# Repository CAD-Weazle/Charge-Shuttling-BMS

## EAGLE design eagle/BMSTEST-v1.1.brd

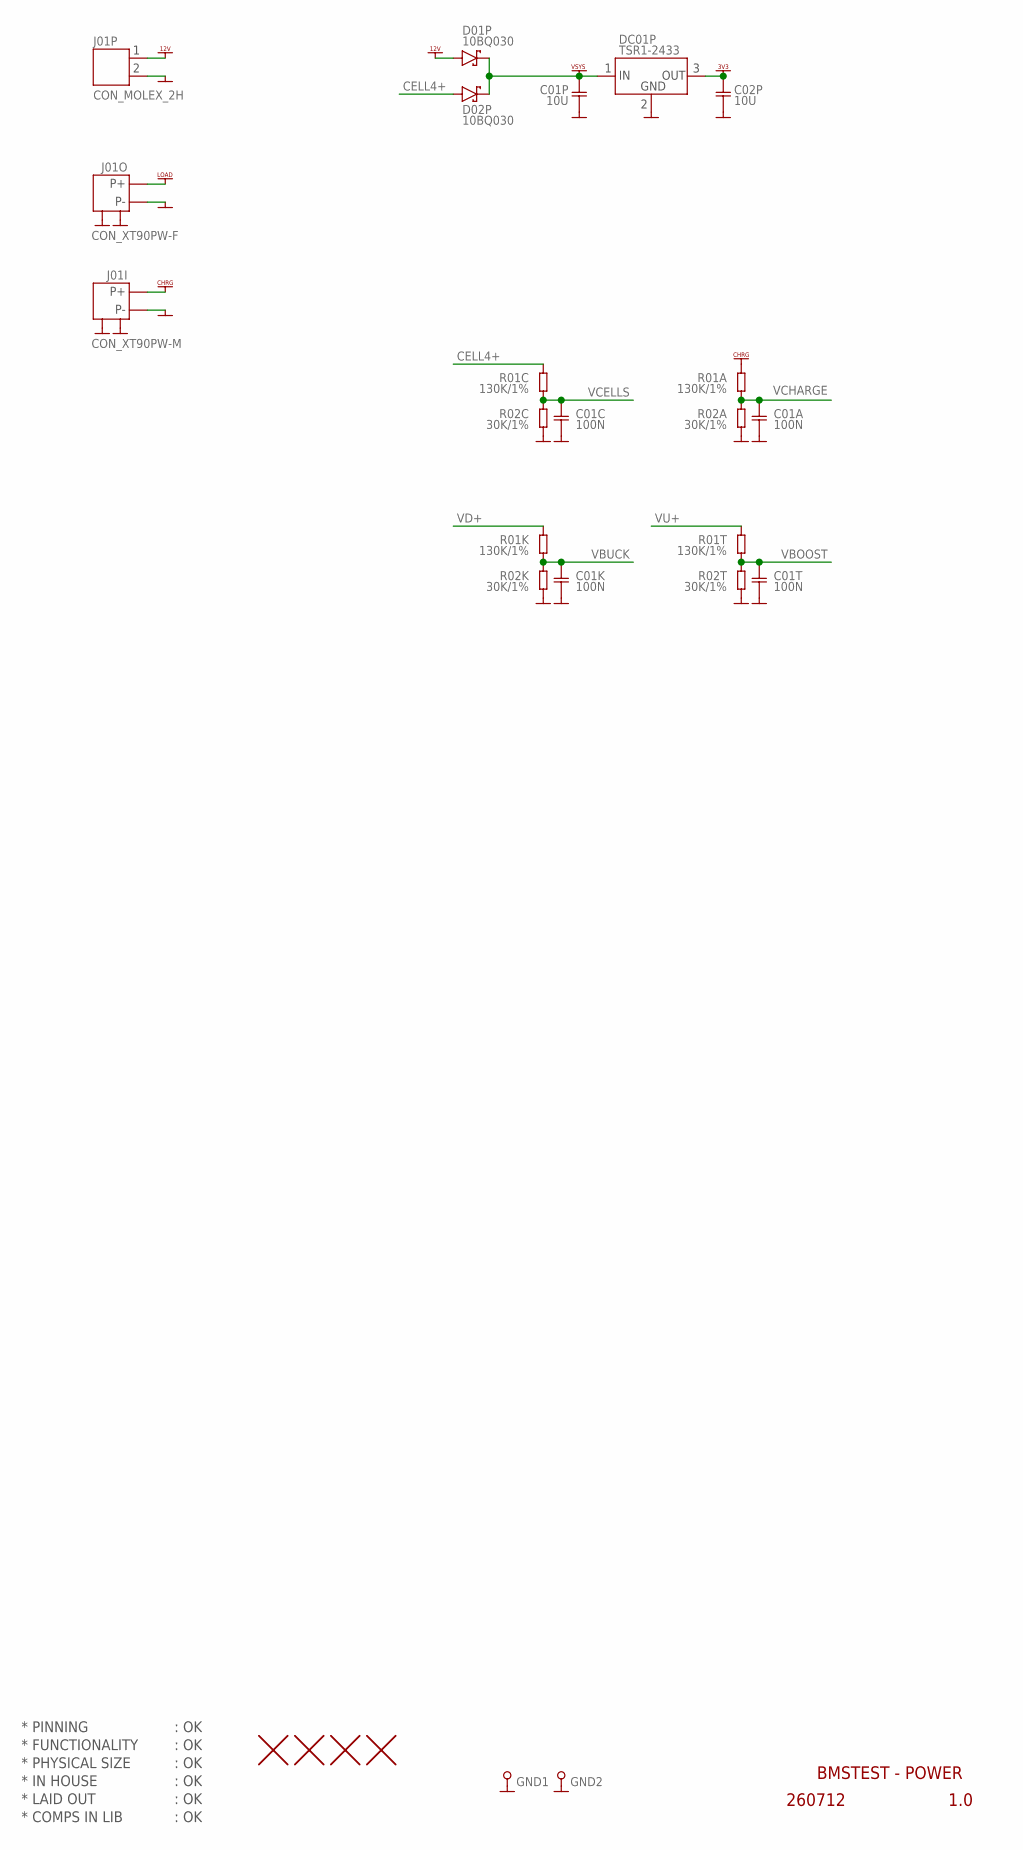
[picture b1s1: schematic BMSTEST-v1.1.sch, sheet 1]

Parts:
C01A, C01C: 100N; CAP0805
C01K, C01T: 100N; CAP0603
C01P, C02P: 10U; CAP0805
D01P, D02P: 10BQ030; DIODE_SMB
DC01P: TSR1-2433
GND1, GND2: PIN_TEST; HOLE_PTH_0.8MM
H1, H2, H3, H4: HOLE_NPTH_3.2MM
J01I: CON_XT90PW-M
J01O: CON_XT90PW-F
J01P: CON_MOLEX_2H
R01A, R01C: 130K/1%; RES0805
R01K, R01T: 130K/1%; RES0603
R02A, R02C: 30K/1%; RES0805
R02K, R02T: 30K/1%; RES0603

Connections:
CELL4+: D02P.A (+), R01C.2; also elsewhere on the board
GND: C01A.2, C01C.2, C01K.2, C01P.2, C01T.2, C02P.2, DC01P.2 (2.GND), GND1.1, GND2.1, J01I.-, J01I.CASE1, J01I.CASE2, J01O.-, J01O.CASE1, J01O.CASE2, J01P.2, R02A.1, R02C.1, R02K.1, R02T.1; also elsewhere on the board
VBOOST: C01T.1, R01T.1, R02T.2; also elsewhere on the board
VBUCK: C01K.1, R01K.1, R02K.2; also elsewhere on the board
VCELLS: C01C.1, R01C.1, R02C.2; also elsewhere on the board
VCHARGE: C01A.1, R01A.1, R02A.2; also elsewhere on the board
VD+: R01K.2; also elsewhere on the board
VDD_3V3: C02P.1, DC01P.3 (3.OUT); also elsewhere on the board
VDD_12V: D01P.A (+), J01P.1
VSYS: C01P.1, D01P.C (-), D02P.C (-), DC01P.1 (1.IN); also elsewhere on the board
VU+: R01T.2; also elsewhere on the board
V_CHARGER: J01I.+, R01A.2; also elsewhere on the board
V_LOAD: J01O.+; also elsewhere on the board

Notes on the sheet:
* PINNING
* FUNCTIONALITY
* PHYSICAL SIZE
* LAID OUT
* COMPS IN LIB
* IN HOUSE
BMSTEST - POWER
260712
1.0
: OK

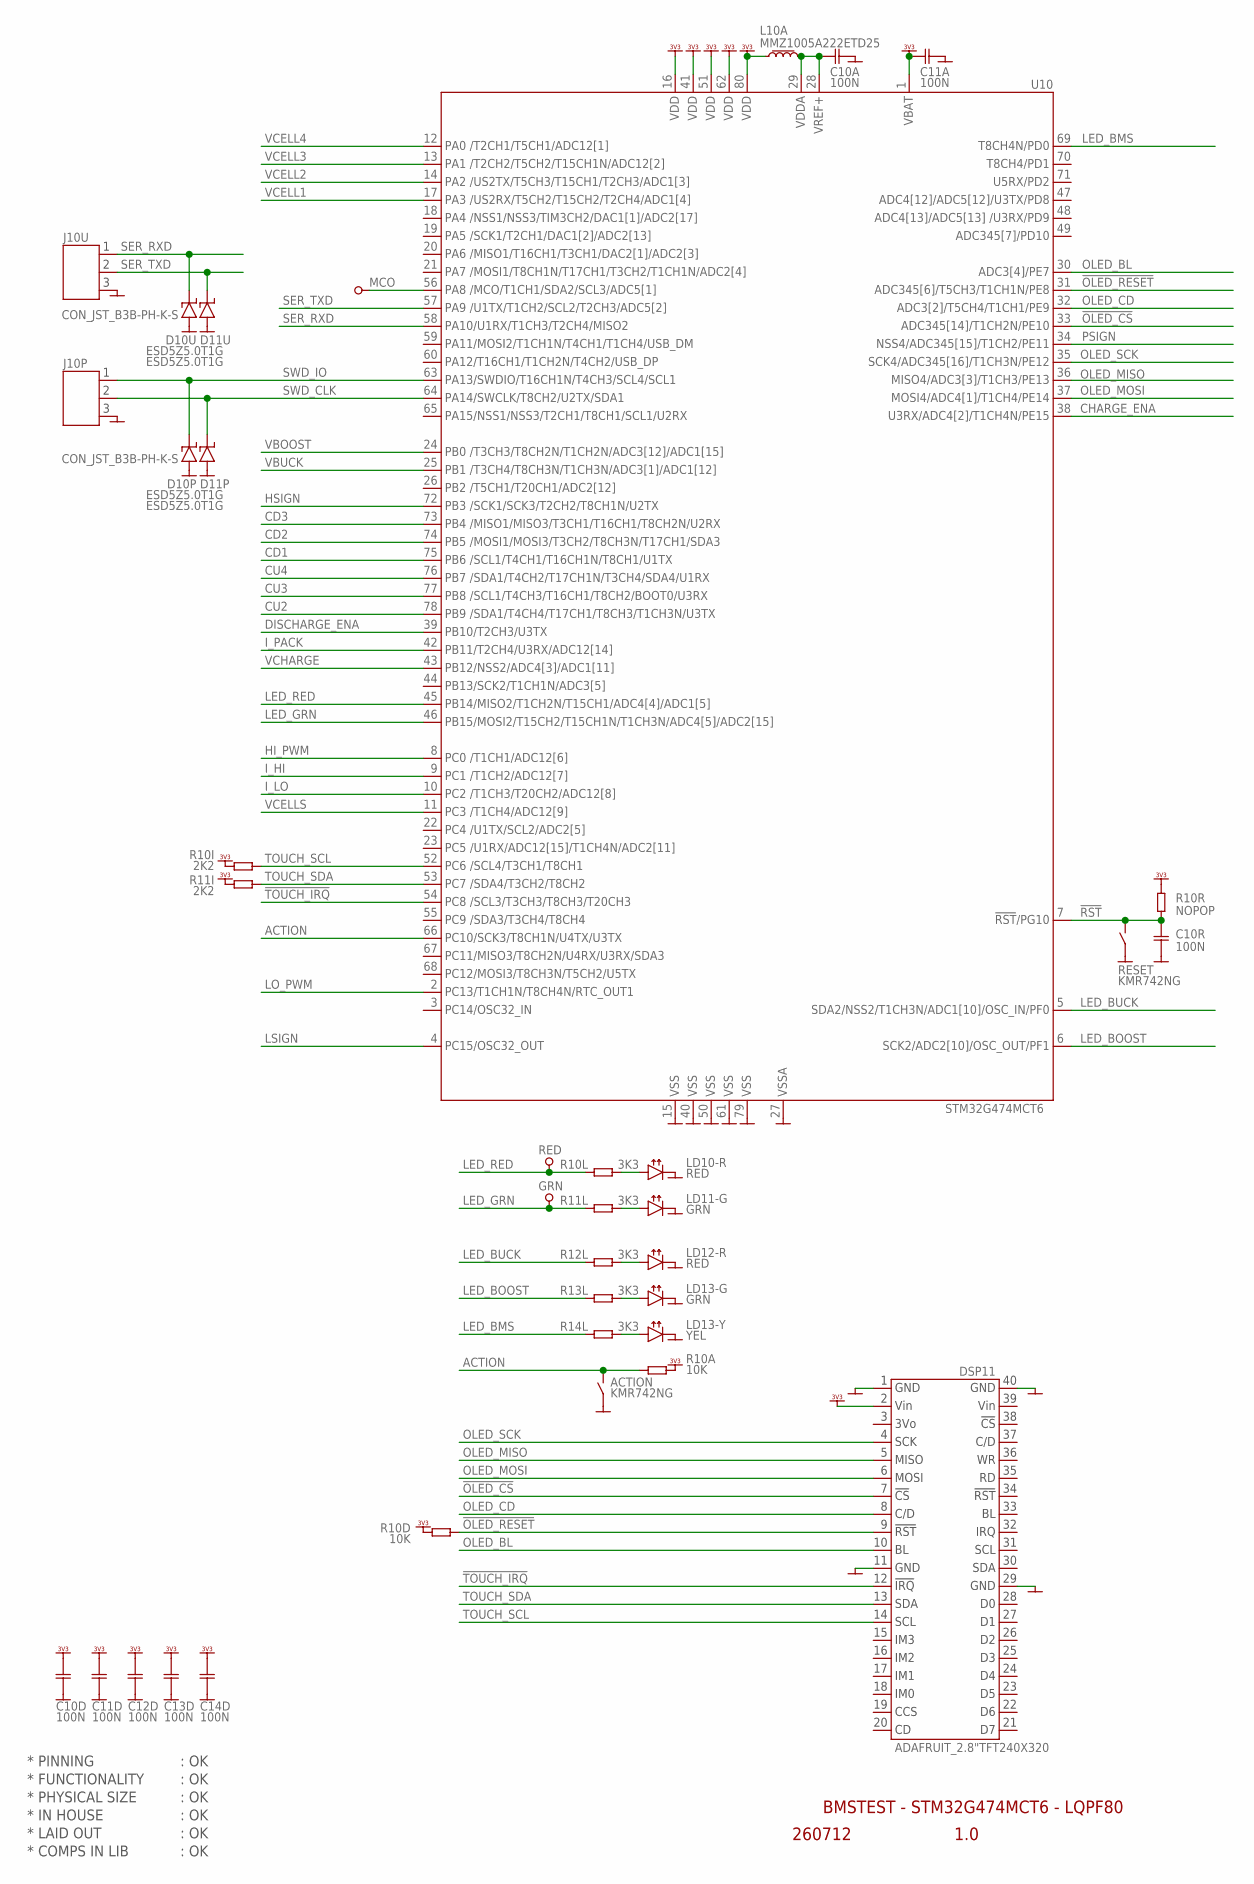
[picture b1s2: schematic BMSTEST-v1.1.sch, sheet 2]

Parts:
ACTION: KMR742NG; SWITCH_PUSHBUTTON_KMR742NG
C10A, C10D, C11A, C11D, C12D, C13D, C14D: 100N; CAP0402
C10R: 100N; CAP0603
D10P, D10U, D11P, D11U: ESD5Z5.0T1G; DIODE_SOD523
DSP11: ADAFRUIT_2.8"TFT240X320
GRN: PIN_TEST; HOLE_PTH_0.8MM
J10P, J10U: CON_JST_B3B-PH-K-S
L10A: MMZ1005A222ETD25; L_0402
LD10-R, LD12-R: RED; LED_SMD_0603
LD11-G, LD13-G: GRN; LED_SMD_0603
LD13-Y: YEL; LED_SMD_0603
MCO: PIN_TEST; HOLE_PTH_0.8MM
R10A, R10D: 10K; RES0603
R10I, R11I: 2K2; RES0402
R10L, R11L, R12L, R13L, R14L: 3K3; RES0603
R10R: NOPOP; RES0603
RED: PIN_TEST; HOLE_PTH_0.8MM
RESET: KMR742NG; SWITCH_PUSHBUTTON_KMR742NG
U10: STM32G474MCT6; LQFP80

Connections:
!OLED_CS: DSP11.7 (7.CS), U10.33 (33.PE10)
!OLED_RESET: DSP11.9 (9.!RST), R10D.2, U10.31 (31.PE8)
!RST: C10R.1, R10R.1, RESET.1, RESET.4 (1), U10.7 (7.!RST)
!TOUCH_IRQ: DSP11.12 (12.IRQ), U10.54 (54.PC8)
ACTION: ACTION.1, ACTION.4 (1), R10A.1, U10.66 (66.PC10)
CD1: U10.75 (75.PB6); also elsewhere on the board
CD2: U10.74 (74.PB5); also elsewhere on the board
CD3: U10.73 (73.PB4); also elsewhere on the board
CHARGE_ENA: U10.38 (38.PE15); also elsewhere on the board
CU2: U10.78 (78.PB9); also elsewhere on the board
CU3: U10.77 (77.PB8); also elsewhere on the board
CU4: U10.76 (76.PB7); also elsewhere on the board
DISCHARGE_ENA: U10.39 (39.PB10); also elsewhere on the board
GND: ACTION.2, ACTION.3 (2), C10A.2, C10D.2, C10R.2, C11A.2, C11D.2, C12D.2, C13D.2, C14D.2, D10P.A, D10U.A, D11P.A, D11U.A, DSP11.1 (1.GND), DSP11.11 (11.GND), DSP11.29 (29.GND), DSP11.40 (40.GND), J10P.3, J10U.3, LD10-R.C, LD11-G.C, LD12-R.C, LD13-G.C, LD13-Y.C, RESET.2, RESET.3 (2), U10.15 (15.VSS), U10.27 (27.VSSA), U10.40 (40.VSS), U10.50 (50.VSS), U10.61 (61.VSS), U10.79 (79.VSS); also elsewhere on the board
HI_PWM: U10.8 (8.PC0); also elsewhere on the board
HSIGN: U10.72 (72.PB3); also elsewhere on the board
I_HI: U10.9 (9.PC1); also elsewhere on the board
I_LO: U10.10 (10.PC2); also elsewhere on the board
I_PACK: U10.42 (42.PB11); also elsewhere on the board
LED_BMS: R14L.1, U10.69 (69.PD0)
LED_BOOST: R13L.1, U10.6 (6.OSC_OUT)
LED_BUCK: R12L.1, U10.5 (5.OSC_IN)
LED_GRN: GRN.1, R11L.1, U10.46 (46.PB15)
LED_RED: R10L.1, RED.1, U10.45 (45.PB14)
LO_PWM: U10.2 (2.PC13); also elsewhere on the board
LSIGN: U10.4 (4.PC15); also elsewhere on the board
MCO: MCO.1, U10.56 (56.PA8)
unnamed: LD13-Y.A, R14L.2
unnamed: LD11-G.A, R11L.2
unnamed: LD12-R.A, R12L.2
unnamed: LD13-G.A, R13L.2
unnamed: LD10-R.A, R10L.2
OLED_BL: DSP11.10 (10.BL), U10.30 (30.PE7)
OLED_CD: DSP11.8 (8.D/C), U10.32 (32.PE9)
OLED_MISO: DSP11.5 (5.MISO), U10.36 (36.PE13)
OLED_MOSI: DSP11.6 (6.MOSI), U10.37 (37.PE14)
OLED_SCK: DSP11.4 (4.SCK), U10.35 (35.PE12)
PSIGN: U10.34 (34.PE11); also elsewhere on the board
SER_RXD: D10U.C, J10U.1, U10.58 (58.PA10)
SER_TXD: D11U.C, J10U.2, U10.57 (57.PA9)
SWD_CLK: D11P.C, J10P.2, U10.64 (64.PA14)
SWD_IO: D10P.C, J10P.1, U10.63 (63.PA13)
TOUCH_SCL: DSP11.14 (14.SCL), R10I.1, U10.52 (52.PC6)
TOUCH_SDA: DSP11.13 (13.SDA), R11I.1, U10.53 (53.PC7)
VBOOST: U10.24 (24.PB0); also elsewhere on the board
VBUCK: U10.25 (25.PB1); also elsewhere on the board
VCELL1: U10.17 (17.PA3); also elsewhere on the board
VCELL2: U10.14 (14.PA2); also elsewhere on the board
VCELL3: U10.13 (13.PA1); also elsewhere on the board
VCELL4: U10.12 (12.PA0); also elsewhere on the board
VCELLS: U10.11 (11.PC3); also elsewhere on the board
VCHARGE: U10.43 (43.PB12); also elsewhere on the board
VDDA1: C10A.1, L10A.2, U10.28 (28.VREF+), U10.29 (29.VDDA)
VDD_3V3: C10D.1, C11A.1, C11D.1, C12D.1, C13D.1, C14D.1, DSP11.2 (2.VIN), L10A.1, R10A.2, R10D.1, R10I.2, R10R.2, R11I.2, U10.1 (1.VBAT), U10.16 (16.VDD), U10.41 (41.VDD), U10.51 (51.VDD), U10.62 (62.VDD), U10.80 (80.VDD); also elsewhere on the board

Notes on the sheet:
* PINNING
* FUNCTIONALITY
* PHYSICAL SIZE
* LAID OUT
* COMPS IN LIB
* IN HOUSE
BMSTEST - STM32G474MCT6 - LQPF80
260712
1.0
: OK

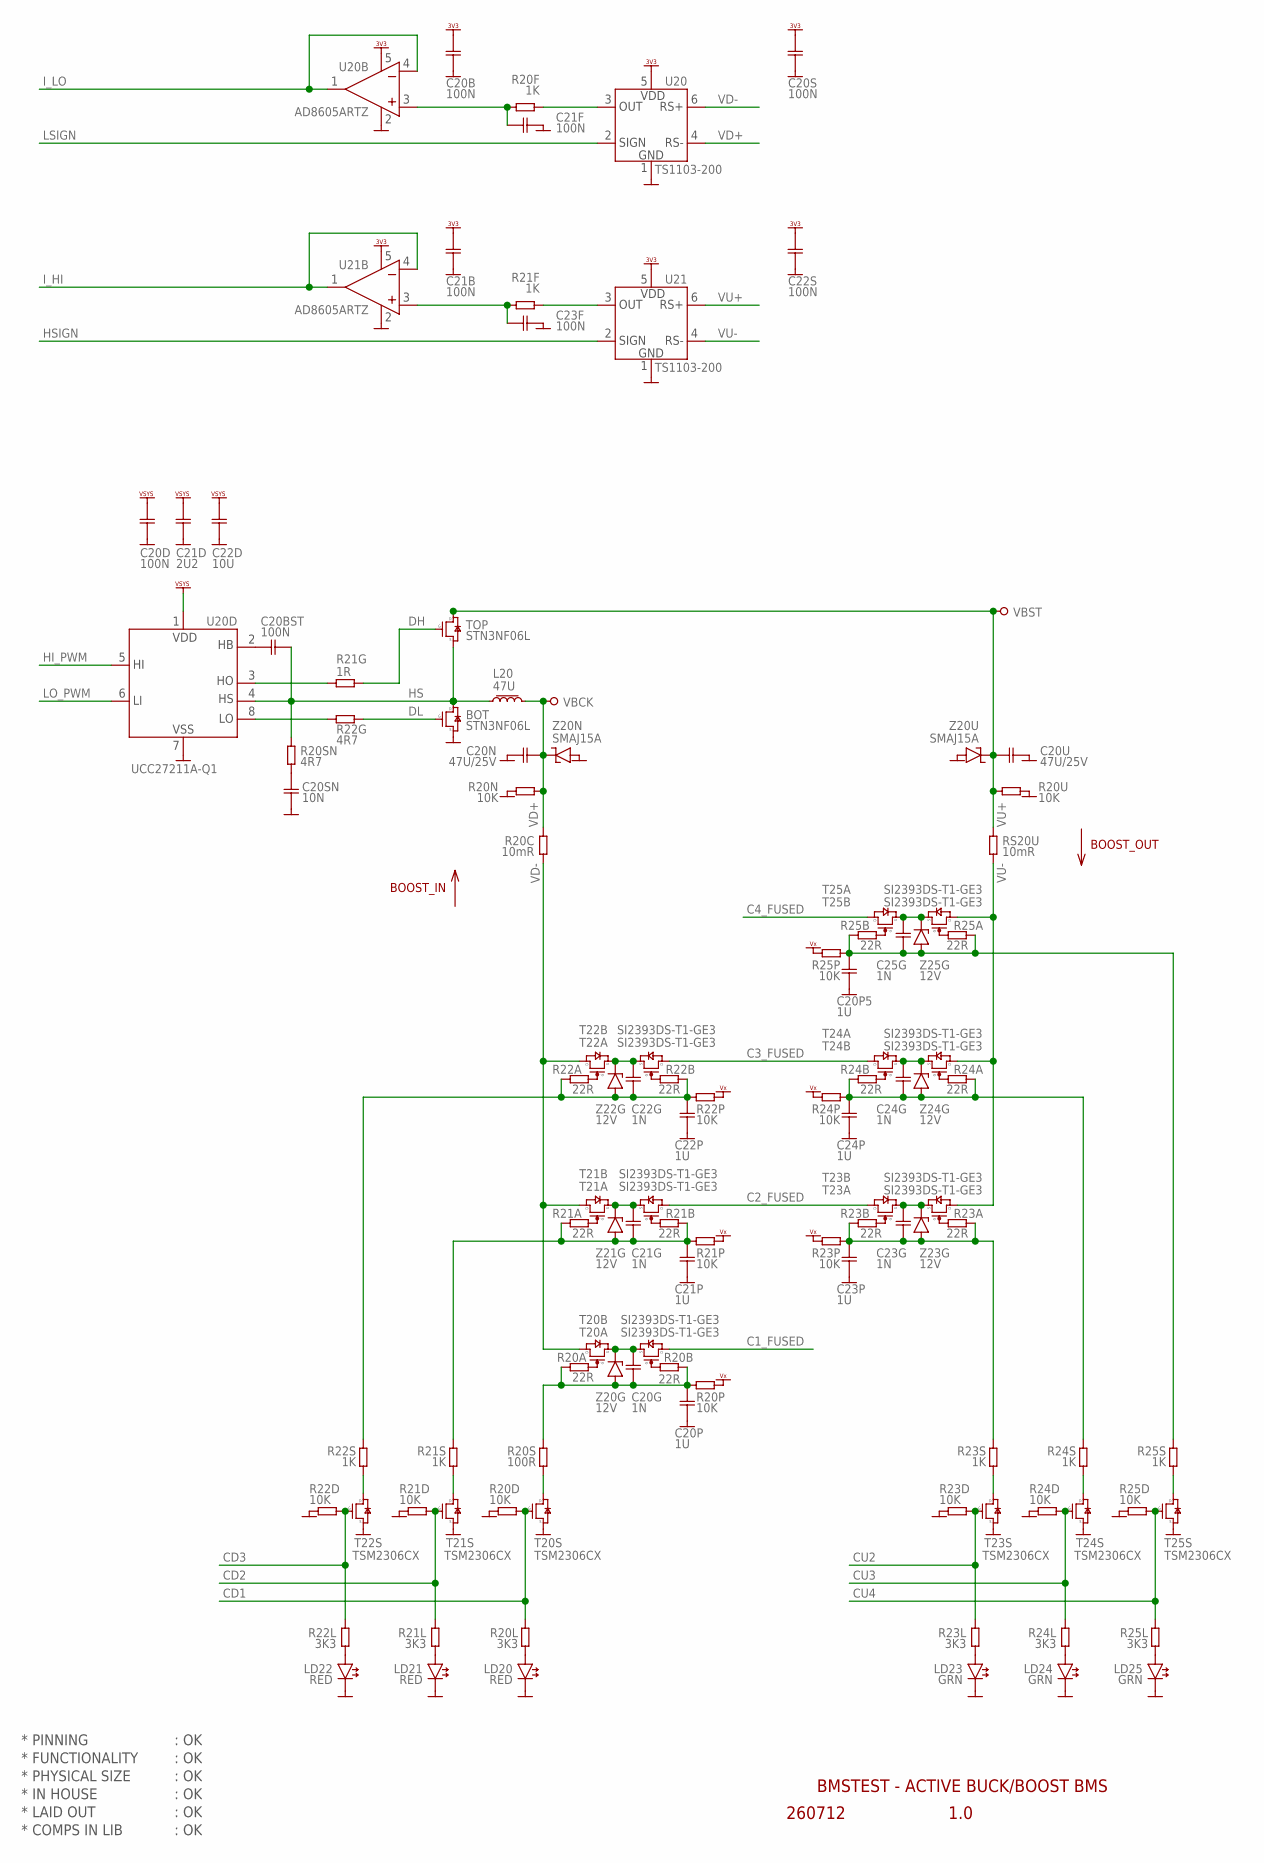
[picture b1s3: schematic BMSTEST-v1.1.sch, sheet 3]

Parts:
BOT: STN3NF06L; SOT223
C20B, C20D, C20S, C21B, C21F, C22S, C23F: 100N; CAP0603
C20BST: 100N; CAP0805
C20G, C21G, C22G, C23G, C24G, C25G: 1N; CAP0603
C20N, C20U: 47U/25V; CAP1210
C20P, C20P5, C21P, C22P, C23P, C24P: 1U; CAP0603
C20SN: 10N; CAP0805
C21D: 2U2; CAP0603
C22D: 10U; CAP0805
L20: 47U; L_WE_HCI_6.9X6.9
LD20, LD21, LD22: RED; LED_SMD_0603
LD23, LD24, LD25: GRN; LED_SMD_0603
R20A, R20B, R21A, R21B, R22A, R22B, R23A, R23B, R24A, R24B, R25A, R25B: 22R; RES0603
R20C: 10mR; RES1206
R20D, R20P, R21D, R21P, R22D, R22P, R23D, R23P, R24D, R24P, R25D, R25P: 10K; RES0603
R20F, R21F, R21S, R22S, R23S, R24S, R25S: 1K; RES0603
R20L, R21L, R22L, R23L, R24L, R25L: 3K3; RES0603
R20N, R20U: 10K; RES0805
R20S: 100R; RES0603
R20SN: 4R7; RES0805
R21G: 1R; RES0508
R22G: 4R7; RES0508
RS20U: 10mR; RES1206
T20A, T20B, T21A, T21B, T22A, T22B, T23A, T23B, T24A, T24B, T25A, T25B: SI2393DS-T1-GE3; PFET_SOT23
T20S, T21S, T22S, T23S, T24S, T25S: TSM2306CX; NFET_SOT23
TOP: STN3NF06L; SOT223
U20, U21: TS1103-200; SOT23-6
U20B, U21B: AD8605ARTZ; SOT23-5
U20D: UCC27211A-Q1; SO8-EP
VBCK: PIN_TEST; HOLE_PTH_0.8MM
VBST: PIN_TEST; HOLE_PTH_0.8MM
Z20G, Z21G, Z22G, Z23G, Z24G, Z25G: 12V; ZENER_SOD80
Z20N, Z20U: SMAJ15A; DIODE_SMA_UNI

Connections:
C1_FUSED: T20B.3 (D); also elsewhere on the board
C2_FUSED: T21B.3 (D), T23B.3 (D); also elsewhere on the board
C3_FUSED: T22B.3 (D), T24B.3 (D); also elsewhere on the board
C4_FUSED: T25B.3 (D); also elsewhere on the board
CD1: R20D.2, R20L.2, T20S.G (G1); also elsewhere on the board
CD2: R21D.2, R21L.2, T21S.G (G1); also elsewhere on the board
CD3: R22D.2, R22L.2, T22S.G (G1); also elsewhere on the board
CU2: R23D.2, R23L.2, T23S.G (G1); also elsewhere on the board
CU3: R24D.2, R24L.2, T24S.G (G1); also elsewhere on the board
CU4: R25D.2, R25L.2, T25S.G (G1); also elsewhere on the board
DH: R21G.2, TOP.1 (G)
DL: BOT.1 (G), R22G.2
G0: C20G.2, C20P.1, R20A.2, R20B.1, R20P.2, R20S.1, Z20G.1 (A)
G1: C21G.2, C21P.1, R21A.2, R21B.1, R21P.2, R21S.1, Z21G.1 (A)
G2: C22G.2, C22P.1, R22A.2, R22B.1, R22P.2, R22S.1, Z22G.1 (A)
G3: C23G.2, C23P.1, R23A.1, R23B.2, R23P.2, R23S.1, Z23G.1 (A)
G4: C24G.2, C24P.1, R24A.1, R24B.2, R24P.2, R24S.1, Z24G.1 (A)
G5: C20P5.1, C25G.2, R25A.1, R25B.2, R25P.2, R25S.1, Z25G.1 (A)
GND: BOT.3 (S), C20B.2, C20D.2, C20N.1, C20P.2, C20P5.2, C20S.2, C20SN.2, C20U.2, C21B.2, C21D.2, C21F.1, C21P.2, C22D.2, C22P.2, C22S.2, C23F.1, C23P.2, C24P.2, LD20.C, LD21.C, LD22.C, LD23.C, LD24.C, LD25.C, R20D.1, R20N.2, R20U.2, R21D.1, R22D.1, R23D.1, R24D.1, R25D.1, T20S.S (S2), T21S.S (S2), T22S.S (S2), T23S.S (S2), T24S.S (S2), T25S.S (S2), U20.1 (1.GND), U20B.2 (2.V-), U20D.7 (7.VSS), U20D.EP (7.VSS), U21.1 (1.GND), U21B.2 (2.V-), Z20N.2 (A), Z20U.2 (A); also elsewhere on the board
HB: C20BST.1, U20D.2 (2.HB)
HI_PWM: U20D.5 (5.HI); also elsewhere on the board
HO: R21G.1, U20D.3 (3.HO)
HS: BOT.2 (D), BOT.4 (D1), C20BST.2, L20.1, R20SN.1, TOP.3 (S), U20D.4 (4.HS)
HSIGN: U21.2 (2.SIGN); also elsewhere on the board
I_HI: U21B.1 (1.OUT), U21B.4 (4.IN-); also elsewhere on the board
I_HI*: C23F.2, R21F.2, U21B.3 (3.IN+)
I_LO: U20B.1 (1.OUT), U20B.4 (4.IN-); also elsewhere on the board
I_LO*: C21F.2, R20F.2, U20B.3 (3.IN+)
LO: R22G.1, U20D.8 (8.LO)
LO_PWM: U20D.6 (6.LI); also elsewhere on the board
LSIGN: U20.2 (2.SIGN); also elsewhere on the board
unnamed: LD22.A, R22L.1
unnamed: LD21.A, R21L.1
unnamed: R23B.1, T23B.1 (G)
unnamed: LD20.A, R20L.1
unnamed: R24B.1, T24B.1 (G)
unnamed: R21A.1, T21A.1 (G)
unnamed: R21B.2, T21B.1 (G)
unnamed: R20A.1, T20A.1 (G)
unnamed: R22B.2, T22B.1 (G)
unnamed: R20B.2, T20B.1 (G)
unnamed: R22A.1, T22A.1 (G)
unnamed: R23A.2, T23A.1 (G)
unnamed: R25B.1, T25B.1 (G)
unnamed: R24A.2, T24A.1 (G)
unnamed: R22S.2, T22S.D (D3)
unnamed: R21S.2, T21S.D (D3)
unnamed: R20S.2, T20S.D (D3)
unnamed: R25A.2, T25A.1 (G)
unnamed: R23S.2, T23S.D (D3)
unnamed: R24S.2, T24S.D (D3)
unnamed: C20SN.1, R20SN.2
unnamed: R25S.2, T25S.D (D3)
unnamed: LD23.A, R23L.1
unnamed: LD24.A, R24L.1
unnamed: LD25.A, R25L.1
unnamed: R20F.1, U20.3 (3.OUT)
unnamed: R21F.1, U21.3 (3.OUT)
S0: C20G.1, T20A.2 (S), T20B.2 (S), Z20G.2 (C)
S1: C21G.1, T21A.2 (S), T21B.2 (S), Z21G.2 (C)
S2: C22G.1, T22A.2 (S), T22B.2 (S), Z22G.2 (C)
S3: C23G.1, T23A.2 (S), T23B.2 (S), Z23G.2 (C)
S4: C24G.1, T24A.2 (S), T24B.2 (S), Z24G.2 (C)
S5: C25G.1, T25A.2 (S), T25B.2 (S), Z25G.2 (C)
VD+: C20N.2, L20.2, R20C.1, R20N.1, U20.4 (4.RS-), VBCK.1, Z20N.1 (C); also elsewhere on the board
VD-: R20C.2, T20A.3 (D), T21A.3 (D), T22A.3 (D), U20.6 (6.RS+)
VDD_3V3: C20B.1, C20S.1, C21B.1, C22S.1, U20.5 (5.VDD), U20B.5 (5.V+), U21.5 (5.VDD), U21B.5 (5.V+); also elsewhere on the board
VSYS: C20D.1, C21D.1, C22D.1, U20D.1 (1.VDD); also elsewhere on the board
VU+: C20U.1, R20U.1, RS20U.1, TOP.2 (D), TOP.4 (D1), U21.6 (6.RS+), VBST.1, Z20U.1 (C); also elsewhere on the board
VU-: RS20U.2, T23A.3 (D), T24A.3 (D), T25A.3 (D), U21.4 (4.RS-)
VX: R20P.1, R21P.1, R22P.1, R23P.1, R24P.1, R25P.1; also elsewhere on the board

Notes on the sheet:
* PINNING
* FUNCTIONALITY
* PHYSICAL SIZE
* LAID OUT
* COMPS IN LIB
* IN HOUSE
BMSTEST - ACTIVE BUCK/BOOST BMS
260712
1.0
: OK
BOOST_OUT
BOOST_IN

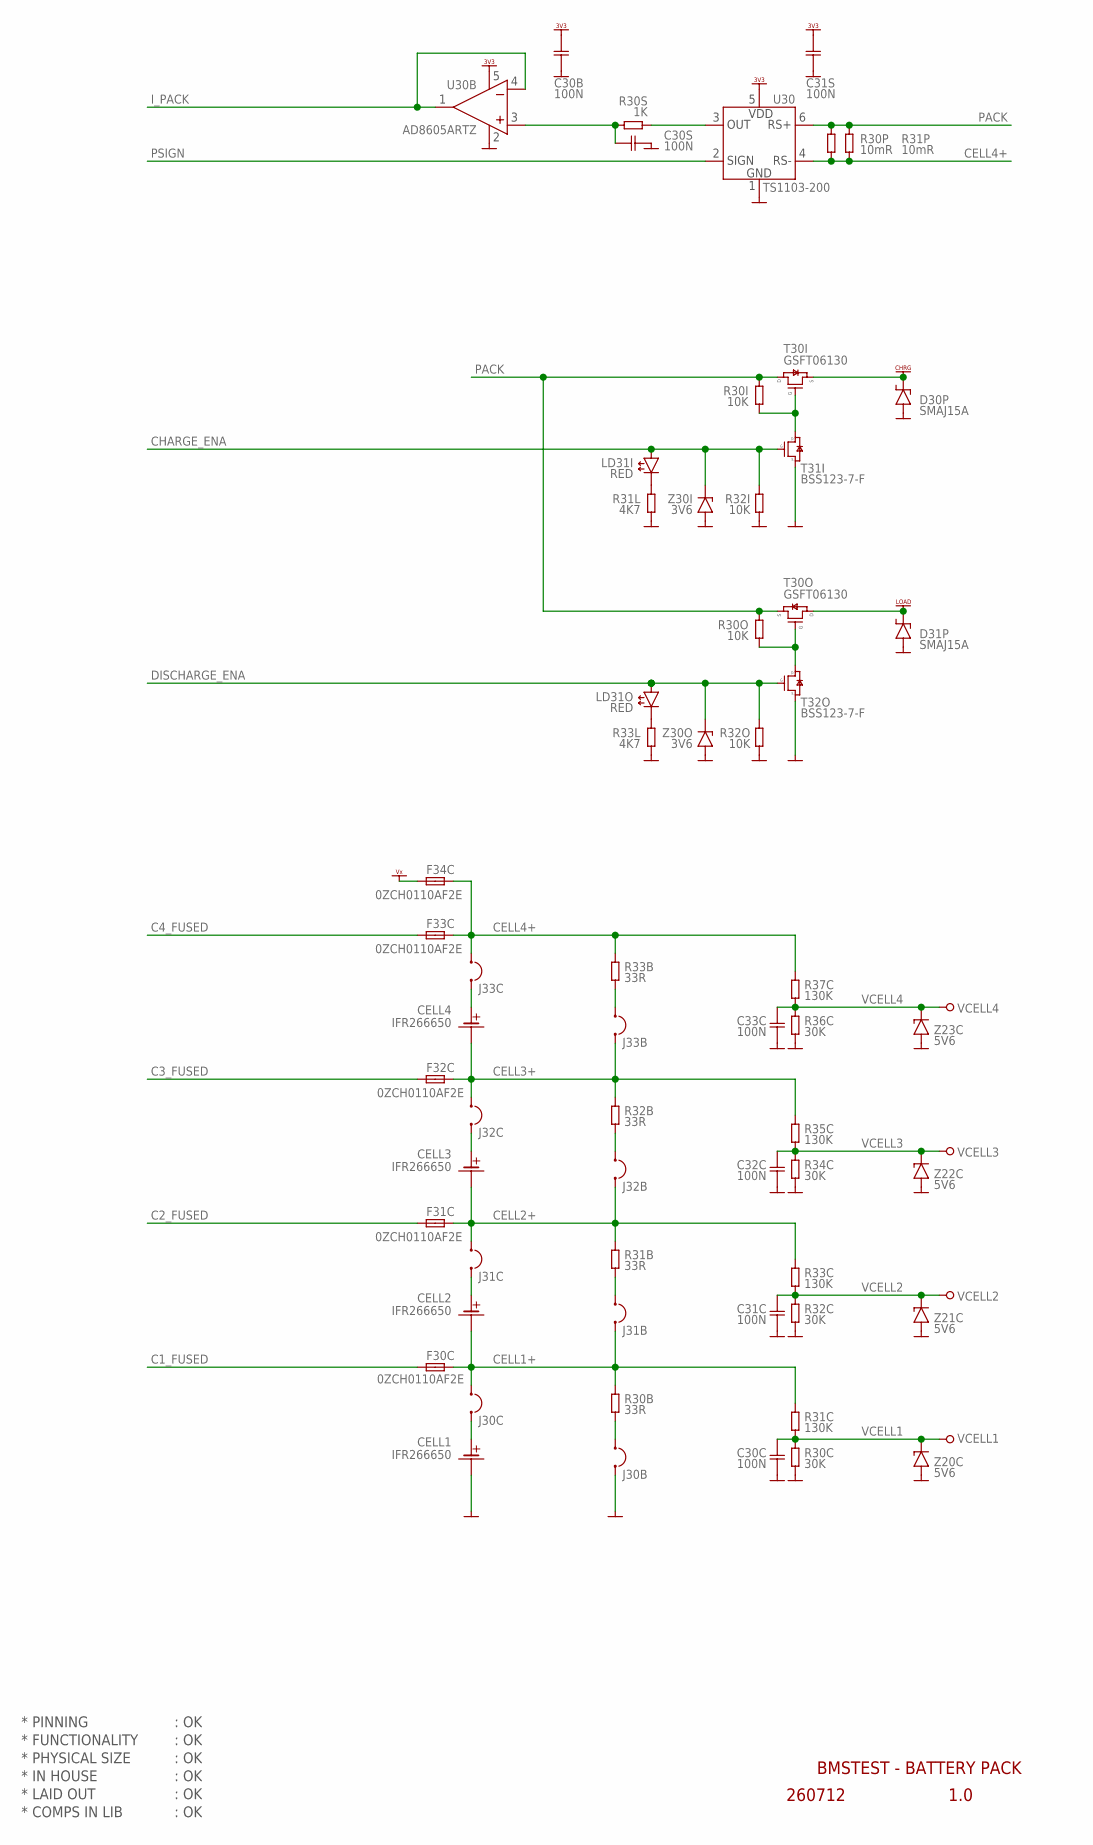
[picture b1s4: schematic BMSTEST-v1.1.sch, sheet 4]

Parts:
C30B, C30S, C31S: 100N; CAP0603
C30C, C31C, C32C, C33C: 100N; CAP0805
CELL1, CELL2, CELL3, CELL4: IFR266650; BATTERY_HOLDER_26650
D30P, D31P: SMAJ15A; DIODE_SMA_UNI
F30C, F31C, F32C, F33C, F34C: 0ZCH0110AF2E; POLYFUSE1210
J30B, J30C, J31B, J31C, J32B, J32C, J33B, J33C: GOLD2
LD31I, LD31O: RED; LED_SMD_0603
R30B, R31B, R32B, R33B: 33R; RES1210
R30C, R32C, R34C, R36C: 30K; RES0805
R30I, R30O, R32I, R32O: 10K; RES0603
R30P, R31P: 10mR; RES1206
R30S: 1K; RES0603
R31C, R33C, R35C, R37C: 130K; RES0805
R31L, R33L: 4K7; RES0603
T30I, T30O: GSFT06130; D2PAK
T31I, T32O: BSS123-7-F; NFET_SOT23
U30: TS1103-200; SOT23-6
U30B: AD8605ARTZ; SOT23-5
VCELL1, VCELL2, VCELL3, VCELL4: PIN_TEST; HOLE_PTH_0.8MM
Z20C, Z21C, Z22C, Z23C: 5V6; ZENER_SOD80
Z30I, Z30O: 3V6; ZENER_SOD80

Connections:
!IN_ON: R30I.2, T30I.1 (G), T31I.D (D3)
!OUT_ON: R30O.2, T30O.1 (G), T32O.D (D3)
C1+: CELL1.+ (1), J30C.1
C1_FUSED: F30C.2; also elsewhere on the board
C2+: CELL2.+ (1), J31C.1
C2_FUSED: F31C.2; also elsewhere on the board
C3+: CELL3.+ (1), J32C.1
C3_FUSED: F32C.2; also elsewhere on the board
C4+: CELL4.+ (1), J33C.1
C4_FUSED: F33C.2; also elsewhere on the board
CELL1+: CELL2.- (2), F30C.1, J30C.2, J31B.1, R30B.2, R31C.1
CELL2+: CELL3.- (2), F31C.1, J31C.2, J32B.1, R31B.2, R33C.1
CELL3+: CELL4.- (2), F32C.1, J32C.2, J33B.1, R32B.2, R35C.1
CELL4+: F33C.1, F34C.1, J33C.2, R30P.2, R31P.2, R33B.2, R37C.1, U30.4 (4.RS-); also elsewhere on the board
CHARGE_ENA: LD31I.A, R32I.1, T31I.G (G1), Z30I.2 (C); also elsewhere on the board
DISCHARGE_ENA: LD31O.A, R32O.1, T32O.G (G1), Z30O.2 (C); also elsewhere on the board
GND: C30B.2, C30C.2, C30S.1, C31C.2, C31S.2, C32C.2, C33C.2, CELL1.- (2), D30P.2 (A), D31P.2 (A), J30B.1, R30C.2, R31L.2, R32C.2, R32I.2, R32O.2, R33L.2, R34C.2, R36C.2, T31I.S (S2), T32O.S (S2), U30.1 (1.GND), U30B.2 (2.V-), Z20C.1 (A), Z21C.1 (A), Z22C.1 (A), Z23C.1 (A), Z30I.1 (A), Z30O.1 (A); also elsewhere on the board
I_LO*1: C30S.2, R30S.2, U30B.3 (3.IN+)
I_PACK: U30B.1 (1.OUT), U30B.4 (4.IN-); also elsewhere on the board
unnamed: R30S.1, U30.3 (3.OUT)
unnamed: LD31I.C, R31L.1
unnamed: LD31O.C, R33L.1
unnamed: J30B.2, R30B.1
unnamed: J31B.2, R31B.1
unnamed: J32B.2, R32B.1
unnamed: J33B.2, R33B.1
PACK: R30I.1, R30O.1, R30P.1, R31P.1, T30I.3 (D), T30O.2 (S), U30.6 (6.RS+)
PSIGN: U30.2 (2.SIGN); also elsewhere on the board
VCELL1: C30C.1, R30C.1, R31C.2, VCELL1.1, Z20C.2 (C); also elsewhere on the board
VCELL2: C31C.1, R32C.1, R33C.2, VCELL2.1, Z21C.2 (C); also elsewhere on the board
VCELL3: C32C.1, R34C.1, R35C.2, VCELL3.1, Z22C.2 (C); also elsewhere on the board
VCELL4: C33C.1, R36C.1, R37C.2, VCELL4.1, Z23C.2 (C); also elsewhere on the board
VDD_3V3: C30B.1, C31S.1, U30.5 (5.VDD), U30B.5 (5.V+); also elsewhere on the board
VX: F34C.2; also elsewhere on the board
V_CHARGER: D30P.1 (C), T30I.2 (S); also elsewhere on the board
V_LOAD: D31P.1 (C), T30O.3 (D); also elsewhere on the board

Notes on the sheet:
* PINNING
* FUNCTIONALITY
* PHYSICAL SIZE
* LAID OUT
* COMPS IN LIB
* IN HOUSE
BMSTEST - BATTERY PACK
260712
1.0
: OK

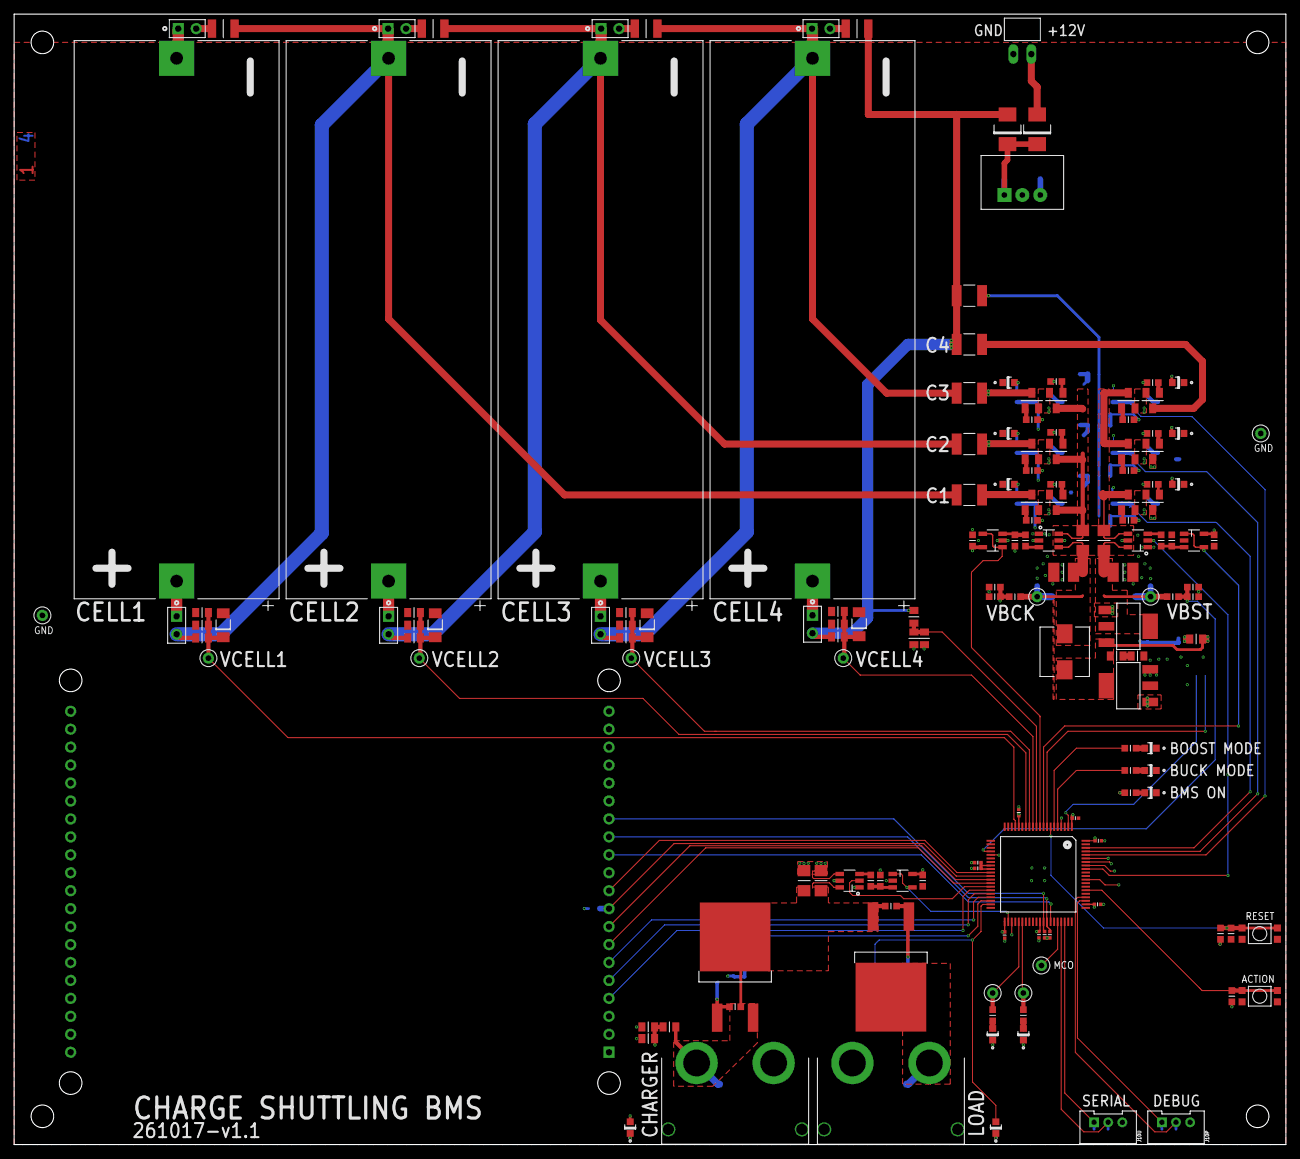
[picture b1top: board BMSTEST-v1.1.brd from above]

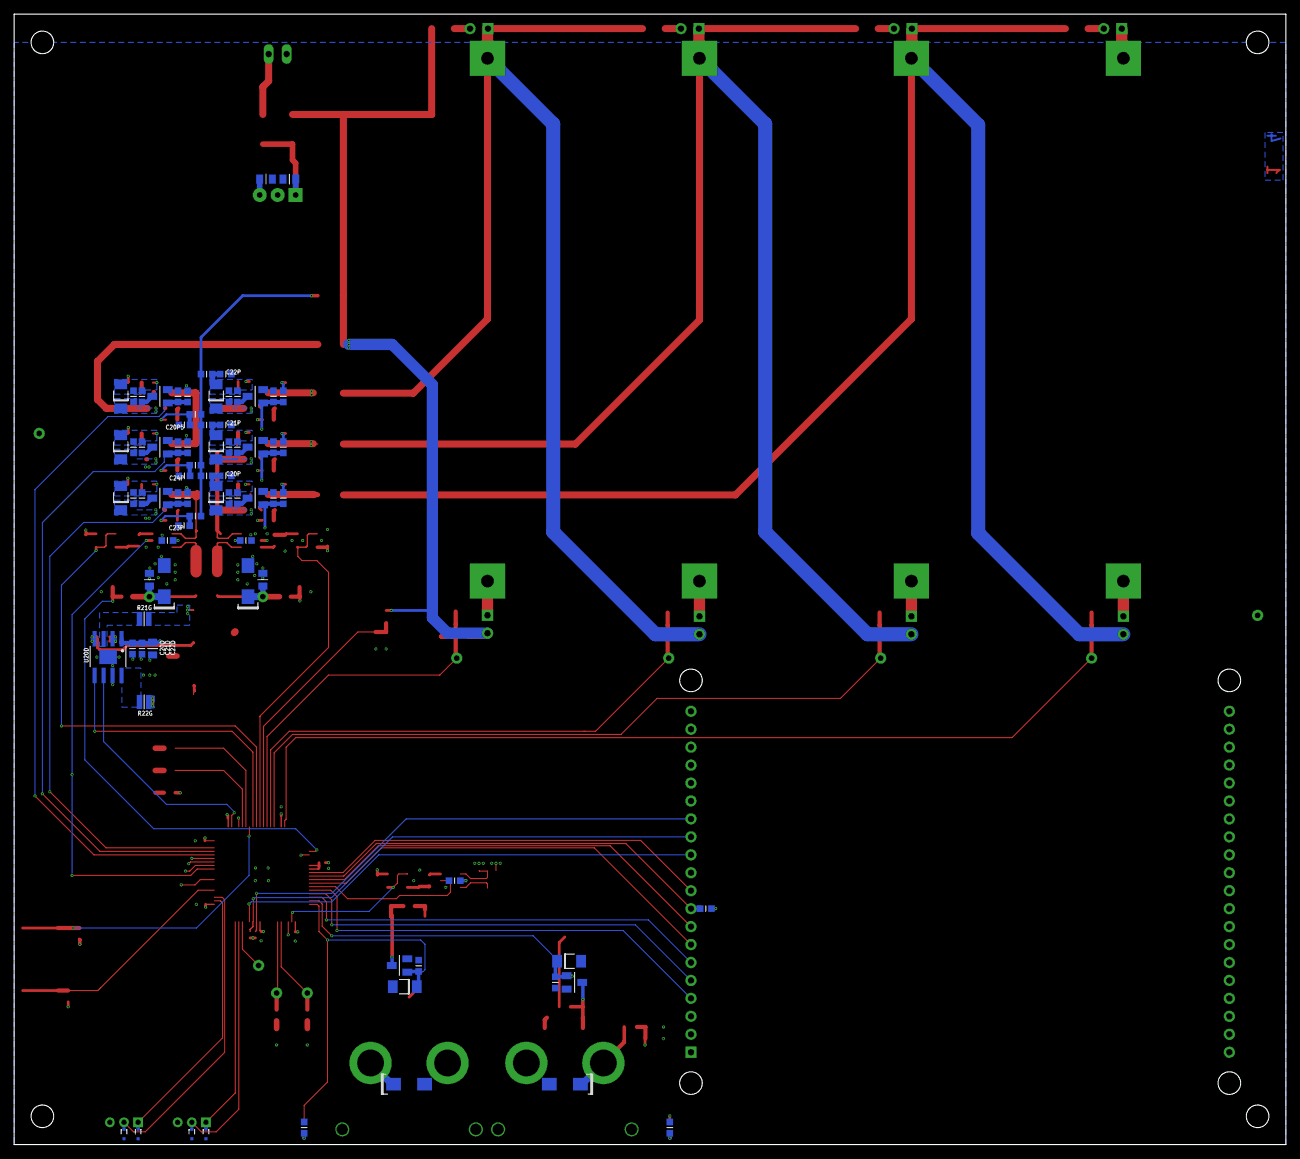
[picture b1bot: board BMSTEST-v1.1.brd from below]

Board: 4 copper layers, 180.0 x 160.0 mm, 240 parts (78 on the bottom side), 133 nets.
